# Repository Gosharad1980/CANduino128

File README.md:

# CANduino128
	- Break-out board pour la carte Olimex AVR-H128-CAN
	- Carte sur base d'AVR AT90CAN128
		- PC104 form factor
		- CAN network
		- SPI
		- I2C
		- bus d'addresse/Data externe via 74AHC373

# Board details

# Other
If you're happy by my work ... put a star ;-)

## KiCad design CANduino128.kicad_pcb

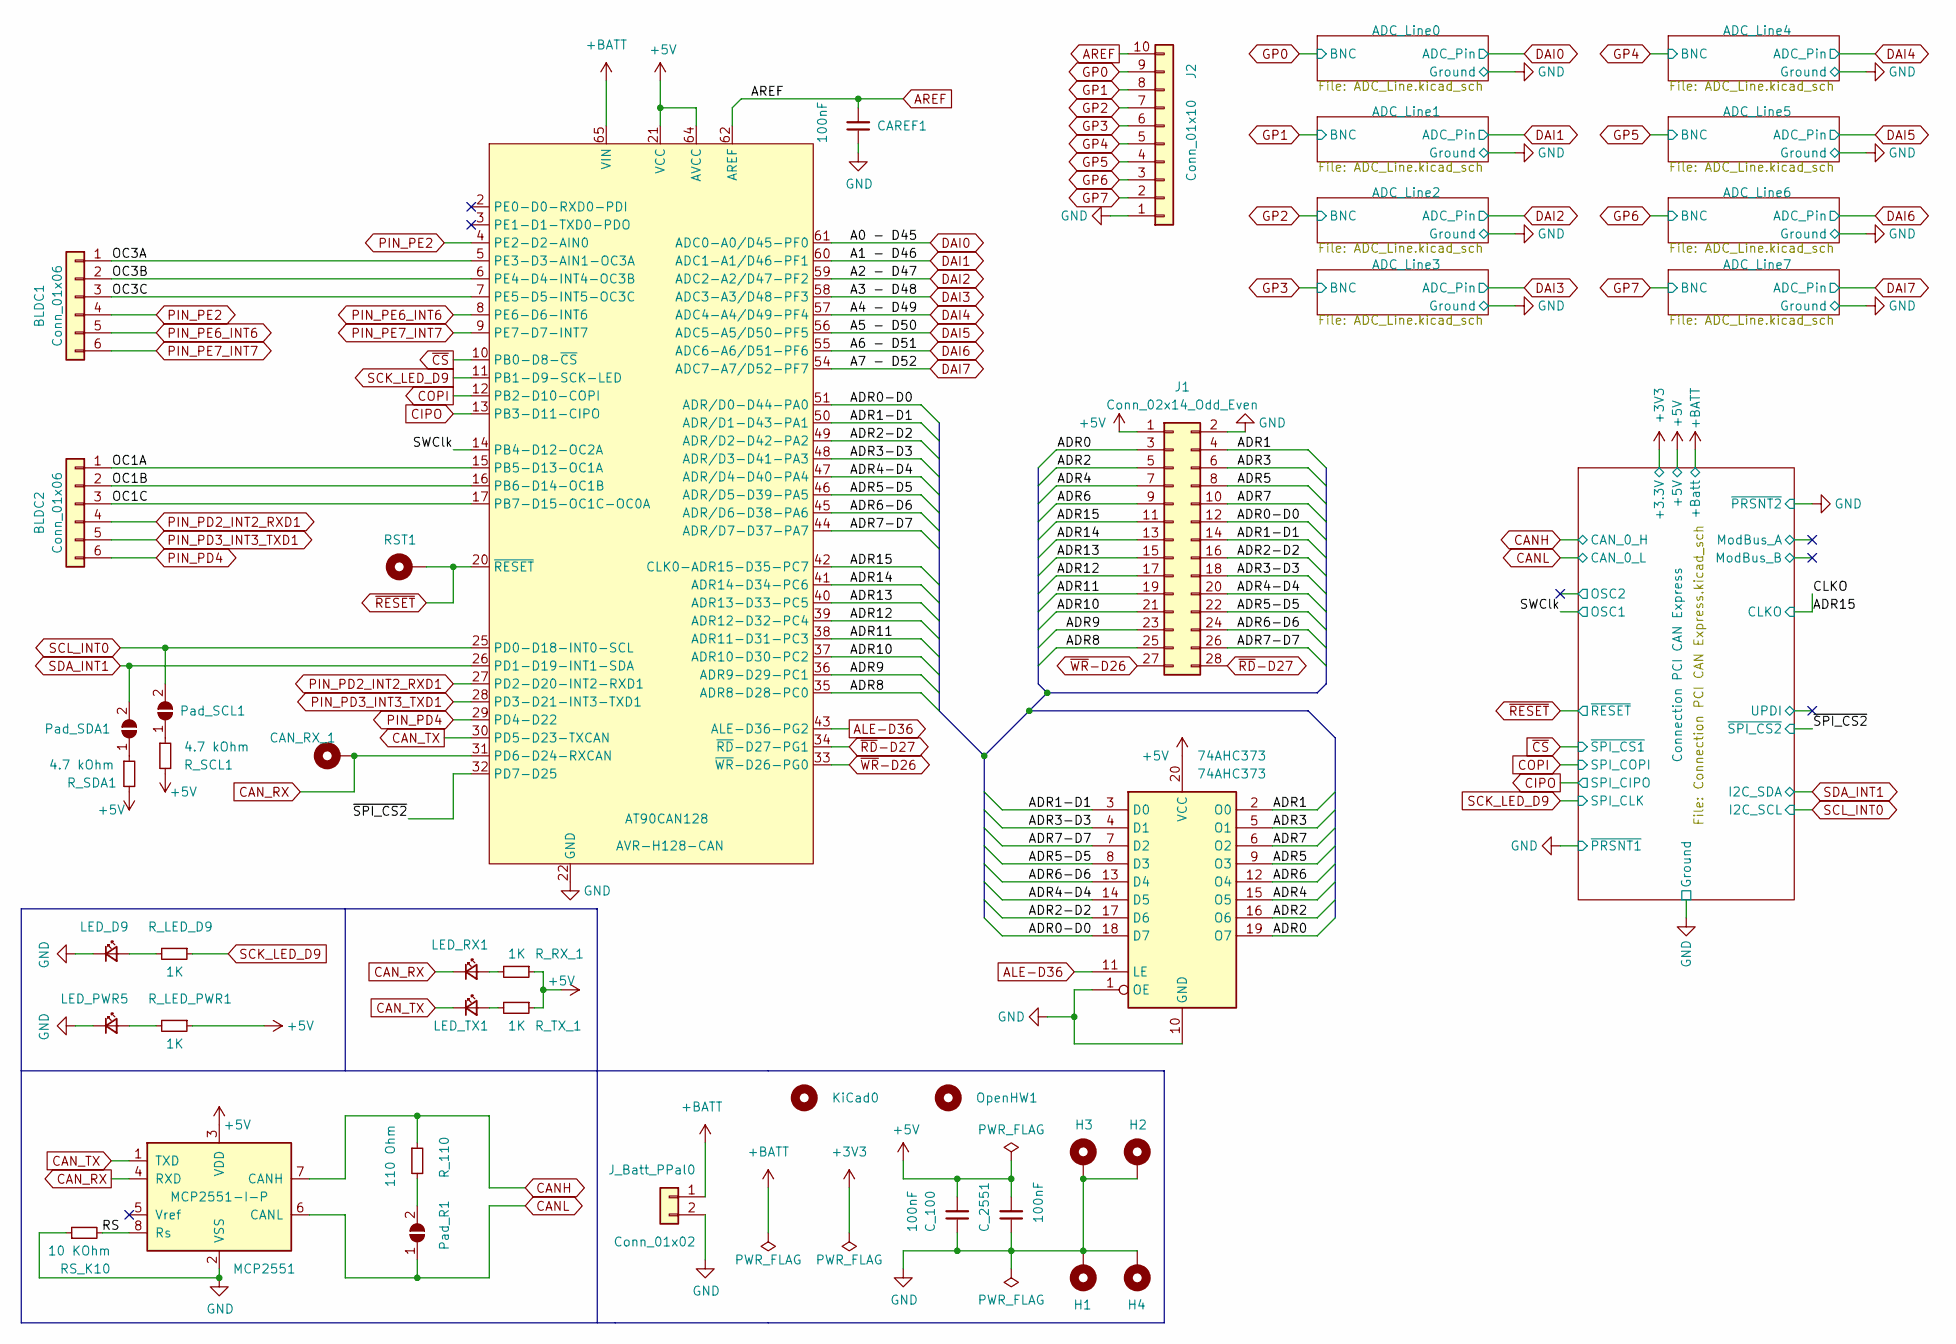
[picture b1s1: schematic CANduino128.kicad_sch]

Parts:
74AHC373: 74AHC373; SO-20_12.8x7.5mm_P1.27mm
AT90CAN128: AVR-H128-CAN; AVR_H128-CAN
BLDC1, BLDC2: Conn_01x06; TerminalBlock_Phoenix_MKDS-1,5-6-5.08_1x06_P5.08mm_Horizont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
CAN_RX_1: MountingHole_Pad; SolderWire-0.1sqmm_1x01_D0.4mm_OD1mm
CAREF1: 100nF; C_1210_3225Metric_Pad1.33x2.70mm_HandSolder
C_100, C_2551: 100nF; C_1210_3225Metric_Pad1.33x2.70mm_HandSolder
H1, H2, H3, H4: MountingHole_Pad; MountingHole_3.2mm_M3_Pad_Via
J1: Conn_02x14_Odd_Even; PinHeader_2x14_P2.54mm_Vertical
J2: Conn_01x10; TerminalBlock_Phoenix_MKDS-1,5-10-5.08_1x10_P5.08mm_Horizon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
J_Batt_PPal0: Conn_01x02; TerminalBlock_TE_282834-2_1x02_P2.54mm_Horizontal
KiCad0: MountingHole; KiCad-Logo2_5mm_SilkScreen
LED_D9: LED; LED_1210_3225Metric_Pad1.42x2.65mm_HandSolder
LED_PWR5: LED; LED_1210_3225Metric_Pad1.42x2.65mm_HandSolder
LED_RX1: LED; LED_1210_3225Metric_Pad1.42x2.65mm_HandSolder
LED_TX1: LED; LED_1210_3225Metric_Pad1.42x2.65mm_HandSolder
MCP2551: MCP2551-I-P; DIP-8_W7.62mm_Socket
OpenHW1: MountingHole; OSHW-Logo2_7.3x6mm_SilkScreen
Pad_R1: SolderJumper_2_Open; PinHeader_1x02_P2.54mm_Vertical
Pad_SCL1: SolderJumper_2_Open; SolderJumper-2_P1.3mm_Open_TrianglePad1.0x1.5mm
Pad_SDA1: SolderJumper_2_Open; SolderJumper-2_P1.3mm_Open_TrianglePad1.0x1.5mm
RST1: MountingHole_Pad; TestPoint_Pad_D1.0mm
RS_K10: 10 KOhm; R_1210_3225Metric_Pad1.30x2.65mm_HandSolder
R_110: 110 Ohm; R_1210_3225Metric_Pad1.30x2.65mm_HandSolder
R_LED_D9: 1K; R_1210_3225Metric_Pad1.30x2.65mm_HandSolder
R_LED_PWR1: 1K; R_1210_3225Metric_Pad1.30x2.65mm_HandSolder
R_RX_1: 1K; R_1210_3225Metric_Pad1.30x2.65mm_HandSolder
R_SCL1: 4.7 kOhm; R_1210_3225Metric_Pad1.30x2.65mm_HandSolder
R_SDA1: 4.7 kOhm; R_1210_3225Metric_Pad1.30x2.65mm_HandSolder
R_TX_1: 1K; R_1210_3225Metric_Pad1.30x2.65mm_HandSolder

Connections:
+5V: 74AHC373.20 (VCC), AT90CAN128.21 (VCC), AT90CAN128.52 (VCC), AT90CAN128.64 (AVCC), C_100.2, C_2551.2, J1.1, MCP2551.3 (VDD), R_LED_PWR1.1, R_RX_1.1, R_SCL1.2, R_SDA1.2, R_TX_1.1; also elsewhere on the board
+BATT: AT90CAN128.65 (VIN), J_Batt_PPal0.1; also elsewhere on the board
/ADR0: 74AHC373.19 (O7), J1.3
/ADR0-D0: 74AHC373.18 (D7), AT90CAN128.51 (ADR/D0-D44-PA0), J1.12
/ADR1: 74AHC373.2 (O0), J1.4
/ADR1-D1: 74AHC373.3 (D0), AT90CAN128.50 (ADR/D1-D43-PA1), J1.14
/ADR2: 74AHC373.16 (O6), J1.5
/ADR2-D2: 74AHC373.17 (D6), AT90CAN128.49 (ADR/D2-D42-PA2), J1.16
/ADR3: 74AHC373.5 (O1), J1.6
/ADR3-D3: 74AHC373.4 (D1), AT90CAN128.48 (ADR/D3-D41-PA3), J1.18
/ADR4: 74AHC373.15 (O5), J1.7
/ADR4-D4: 74AHC373.14 (D5), AT90CAN128.47 (ADR/D4-D40-PA4), J1.20
/ADR5: 74AHC373.9 (O3), J1.8
/ADR5-D5: 74AHC373.8 (D3), AT90CAN128.46 (ADR/D5-D39-PA5), J1.22
/ADR6: 74AHC373.12 (O4), J1.9
/ADR6-D6: 74AHC373.13 (D4), AT90CAN128.45 (ADR/D6-D38-PA6), J1.24
/ADR7: 74AHC373.6 (O2), J1.10
/ADR7-D7: 74AHC373.7 (D2), AT90CAN128.44 (ADR/D7-D37-PA7), J1.26
/ADR8: AT90CAN128.35 (ADR8-D28-PC0), J1.25
/ADR9: AT90CAN128.36 (ADR9-D29-PC1), J1.23
/ADR10: AT90CAN128.37 (ADR10-D30-PC2), J1.21
/ADR11: AT90CAN128.38 (ADR11-D31-PC3), J1.19
/ADR12: AT90CAN128.39 (ADR12-D32-PC4), J1.17
/ADR13: AT90CAN128.40 (ADR13-D33-PC5), J1.15
/ADR14: AT90CAN128.41 (ADR14-D34-PC6), J1.13
/ADR15: AT90CAN128.42 (CLK0-ADR15-D35-PC7), J1.11; also elsewhere on the board
/OC1A: AT90CAN128.15 (PB5-D13-OC1A), BLDC2.1
/OC1B: AT90CAN128.16 (PB6-D14-OC1B), BLDC2.2
/OC1C: AT90CAN128.17 (PB7-D15-OC1C-OC0A), BLDC2.3
/OC3A: AT90CAN128.5 (PE3-D3-AIN1-OC3A), BLDC1.1
/OC3B: AT90CAN128.6 (PE4-D4-INT4-OC3B), BLDC1.2
/OC3C: AT90CAN128.7 (PE5-D5-INT5-OC3C), BLDC1.3
/RS: MCP2551.8 (Rs), RS_K10.2
/SWClk: AT90CAN128.14 (PB4-D12-OC2A); also elsewhere on the board
/~SPI_CS2: AT90CAN128.32 (PD7-D25); also elsewhere on the board
ALE-D36: 74AHC373.11 (LE), AT90CAN128.43 (ALE-D36-PG2)
AREF: AT90CAN128.62 (AREF), CAREF1.2, J2.10
CANH: MCP2551.7 (CANH), R_110.1; also elsewhere on the board
CANL: MCP2551.6 (CANL), Pad_R1.1 (A); also elsewhere on the board
CAN_RX: AT90CAN128.31 (PD6-D24-RXCAN), CAN_RX_1.1 (1_1), LED_RX1.1 (K), MCP2551.4 (RXD)
CAN_TX: AT90CAN128.30 (PD5-D23-TXCAN), LED_TX1.1 (K), MCP2551.1 (TXD)
CIPO: AT90CAN128.13 (PB3-D11-CIPO); also elsewhere on the board
COPI: AT90CAN128.12 (PB2-D10-COPI); also elsewhere on the board
DAI0: AT90CAN128.61 (ADC0-A0/D45-PF0); also elsewhere on the board
DAI1: AT90CAN128.60 (ADC1-A1/D46-PF1); also elsewhere on the board
DAI2: AT90CAN128.59 (ADC2-A2/D47-PF2); also elsewhere on the board
DAI3: AT90CAN128.58 (ADC3-A3/D48-PF3); also elsewhere on the board
DAI4: AT90CAN128.57 (ADC4-A4/D49-PF4); also elsewhere on the board
DAI5: AT90CAN128.56 (ADC5-A5/D50-PF5); also elsewhere on the board
DAI6: AT90CAN128.55 (ADC6-A6/D51-PF6); also elsewhere on the board
DAI7: AT90CAN128.54 (ADC7-A7/D52-PF7); also elsewhere on the board
GND: 74AHC373.1 (OE), 74AHC373.10 (GND), AT90CAN128.22 (GND), AT90CAN128.53 (GND), AT90CAN128.63 (GND), AT90CAN128.66 (PWRGND), CAREF1.1, C_100.1, C_2551.1, H1.1 (1_1), H2.1 (1_1), H3.1 (1_1), H4.1 (1_1), J1.2, J2.1, J_Batt_PPal0.2, LED_D9.1 (K), LED_PWR5.1 (K), MCP2551.2 (VSS), RS_K10.1; also elsewhere on the board
GP0: J2.9; also elsewhere on the board
GP1: J2.8; also elsewhere on the board
GP2: J2.7; also elsewhere on the board
GP3: J2.6; also elsewhere on the board
GP4: J2.5; also elsewhere on the board
GP5: J2.4; also elsewhere on the board
GP6: J2.3; also elsewhere on the board
GP7: J2.2; also elsewhere on the board
unnamed: LED_D9.2 (A), R_LED_D9.2
unnamed: LED_PWR5.2 (A), R_LED_PWR1.2
unnamed: LED_RX1.2 (A), R_RX_1.2
unnamed: LED_TX1.2 (A), R_TX_1.2
unnamed: Pad_R1.2 (B), R_110.2
unnamed: Pad_SCL1.1 (A), R_SCL1.1
unnamed: Pad_SDA1.1 (A), R_SDA1.1
PIN_PD2_INT2_RXD1: AT90CAN128.27 (PD2-D20-INT2-RXD1), BLDC2.4
PIN_PD3_INT3_TXD1: AT90CAN128.28 (PD3-D21-INT3-TXD1), BLDC2.5
PIN_PD4: AT90CAN128.29 (PD4-D22), BLDC2.6
PIN_PE2: AT90CAN128.4 (PE2-D2-AIN0), BLDC1.4
PIN_PE6_INT6: AT90CAN128.8 (PE6-D6-INT6), BLDC1.5
PIN_PE7_INT7: AT90CAN128.9 (PE7-D7-INT7), BLDC1.6
SCK_LED_D9: AT90CAN128.11 (PB1-D9-SCK-LED), R_LED_D9.1; also elsewhere on the board
SCL_INT0: AT90CAN128.25 (PD0-D18-INT0-SCL), Pad_SCL1.2 (B); also elsewhere on the board
SDA_INT1: AT90CAN128.26 (PD1-D19-INT1-SDA), Pad_SDA1.2 (B); also elsewhere on the board
~CS: AT90CAN128.10 (PB0-D8-~CS); also elsewhere on the board
~RD-D27: AT90CAN128.34 (~RD-D27-PG1), J1.28
~RESET: AT90CAN128.20 (~RESET), RST1.1 (1_1); also elsewhere on the board
~WR-D26: AT90CAN128.33 (~WR-D26-PG0), J1.27

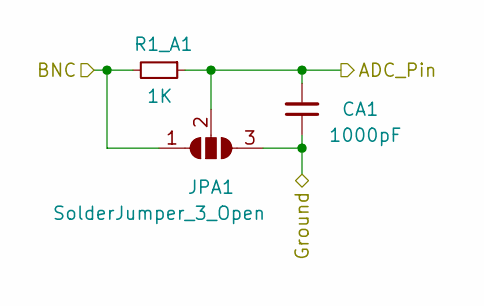
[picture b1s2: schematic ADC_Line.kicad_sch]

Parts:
CA1: 1000pF; C_1210_3225Metric_Pad1.33x2.70mm_HandSolder
JPA1: SolderJumper_3_Open; SolderJumper-3_P1.3mm_Open_RoundedPad1.0x1.5mm
R1_A1: 1K; R_1210_3225Metric_Pad1.30x2.65mm_HandSolder

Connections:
DAI0: CA1.2, JPA1.2 (C), R1_A1.1; also elsewhere on the board
GND: CA1.1, JPA1.3 (B); also elsewhere on the board
GP0: JPA1.1 (A), R1_A1.2; also elsewhere on the board

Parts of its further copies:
CA2, CA3, CA4, CA5, CA6, CA7, CA8: 1000pF; C_1210_3225Metric_Pad1.33x2.70mm_HandSolder
JPA2, JPA3, JPA4, JPA5, JPA6, JPA7, JPA8: SolderJumper_3_Open; SolderJumper-3_P1.3mm_Open_RoundedPad1.0x1.5mm
R1_A2, R1_A3, R1_A4, R1_A5, R1_A6, R1_A7, R1_A8: 1K; R_1210_3225Metric_Pad1.30x2.65mm_HandSolder

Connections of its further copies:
DAI1: CA2.2, JPA2.2 (C), R1_A2.1; also elsewhere on the board
DAI2: CA3.2, JPA3.2 (C), R1_A3.1; also elsewhere on the board
DAI3: CA4.2, JPA4.2 (C), R1_A4.1; also elsewhere on the board
DAI4: CA5.2, JPA5.2 (C), R1_A5.1; also elsewhere on the board
DAI5: CA6.2, JPA6.2 (C), R1_A6.1; also elsewhere on the board
DAI6: CA7.2, JPA7.2 (C), R1_A7.1; also elsewhere on the board
DAI7: CA8.2, JPA8.2 (C), R1_A8.1; also elsewhere on the board
GND: CA2.1, CA3.1, CA4.1, CA5.1, CA6.1, CA7.1, CA8.1, JPA2.3 (B), JPA3.3 (B), JPA4.3 (B), JPA5.3 (B), JPA6.3 (B), JPA7.3 (B), JPA8.3 (B); also elsewhere on the board
GP1: JPA2.1 (A), R1_A2.2; also elsewhere on the board
GP2: JPA3.1 (A), R1_A3.2; also elsewhere on the board
GP3: JPA4.1 (A), R1_A4.2; also elsewhere on the board
GP4: JPA5.1 (A), R1_A5.2; also elsewhere on the board
GP5: JPA6.1 (A), R1_A6.2; also elsewhere on the board
GP6: JPA7.1 (A), R1_A7.2; also elsewhere on the board
GP7: JPA8.1 (A), R1_A8.2; also elsewhere on the board

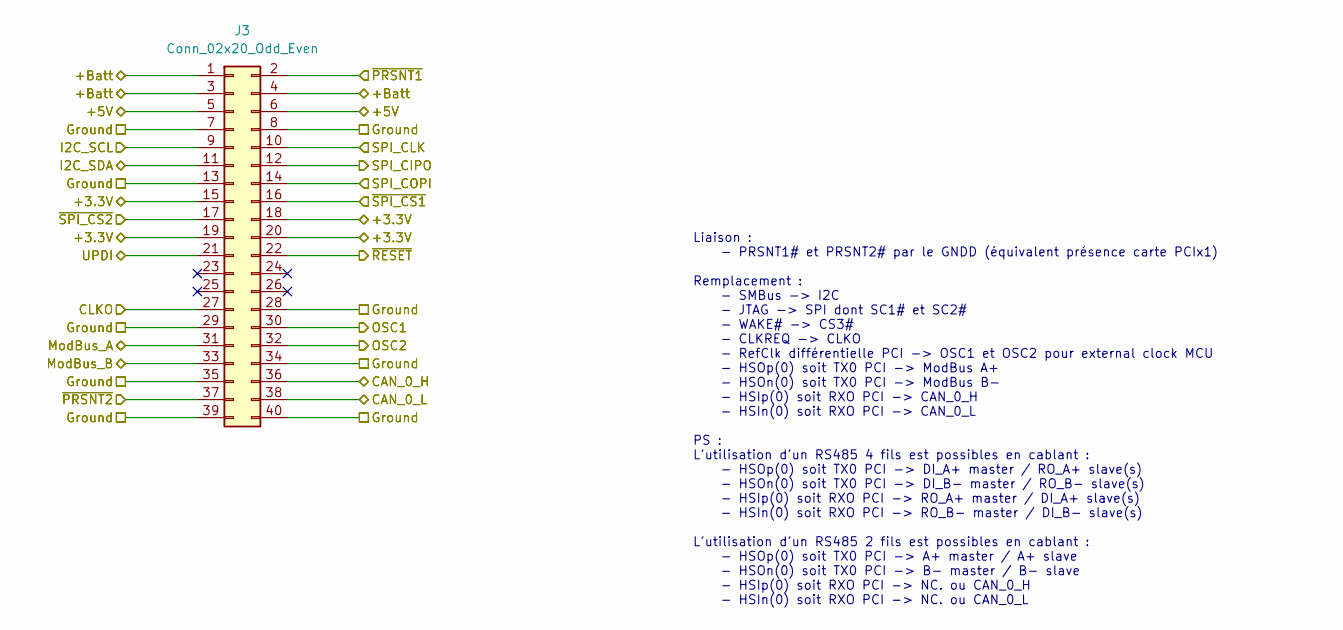
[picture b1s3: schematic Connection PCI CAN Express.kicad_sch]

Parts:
J3: Conn_02x20_Odd_Even; IDC-Header_2x20_P2.54mm_Vertical

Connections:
+3V3: J3.15, J3.18, J3.19, J3.20
+5V: J3.5, J3.6; also elsewhere on the board
+BATT: J3.1, J3.3, J3.4; also elsewhere on the board
/ADR15: J3.27; also elsewhere on the board
/Connection PCI CAN Express/ModBus_A: J3.31
/Connection PCI CAN Express/ModBus_B: J3.33
/Connection PCI CAN Express/OSC2: J3.32
/Connection PCI CAN Express/UPDI: J3.21
/SWClk: J3.30; also elsewhere on the board
/~SPI_CS2: J3.17; also elsewhere on the board
CANH: J3.36; also elsewhere on the board
CANL: J3.38; also elsewhere on the board
CIPO: J3.12; also elsewhere on the board
COPI: J3.14; also elsewhere on the board
GND: J3.2, J3.7, J3.8, J3.13, J3.28, J3.29, J3.34, J3.35, J3.37, J3.39, J3.40; also elsewhere on the board
SCK_LED_D9: J3.10; also elsewhere on the board
SCL_INT0: J3.9; also elsewhere on the board
SDA_INT1: J3.11; also elsewhere on the board
~CS: J3.16; also elsewhere on the board
~RESET: J3.22; also elsewhere on the board

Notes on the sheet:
Liaison : - PRSNT1# et PRSNT2# par le GNDD (équivalent présence carte PCIx1) Remplacement : - SMBus -> I2C - JTAG -> SPI dont SC1# et SC2# - WAKE# -> CS3# - CLKREQ -> CLKO - RefClk différentielle PCI -> OSC1 et OSC2 pour external clock MCU - HSOp(0) soit TX0 PCI -> ModBus A+ - HSOn(0) soit TX0 PCI 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

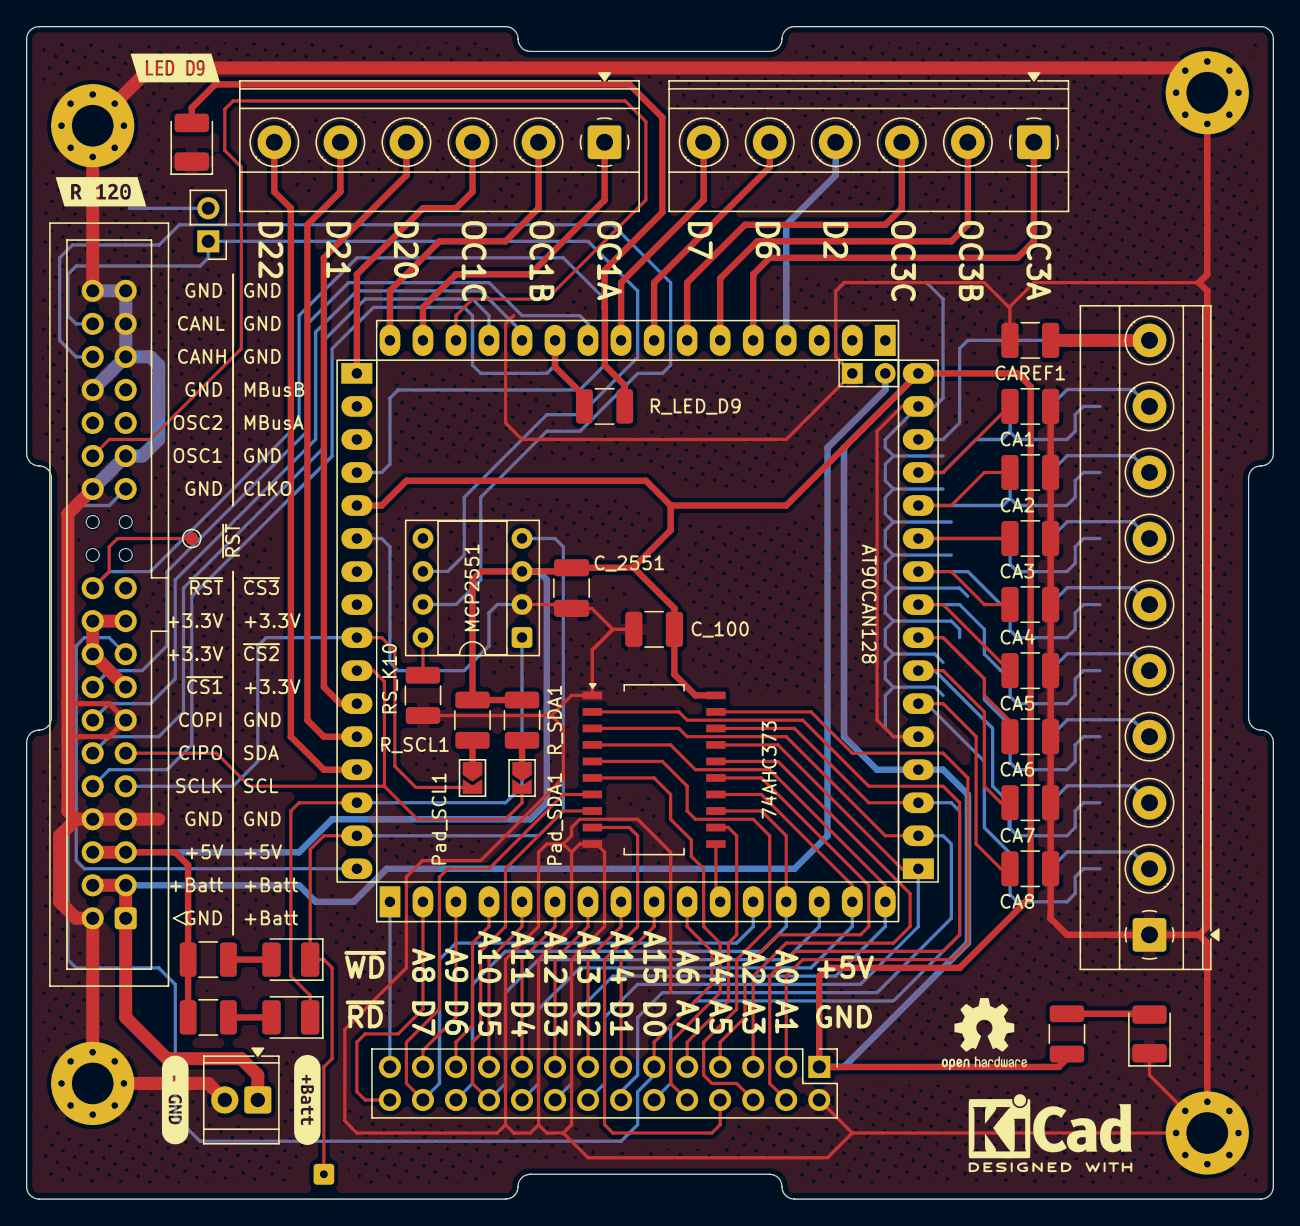
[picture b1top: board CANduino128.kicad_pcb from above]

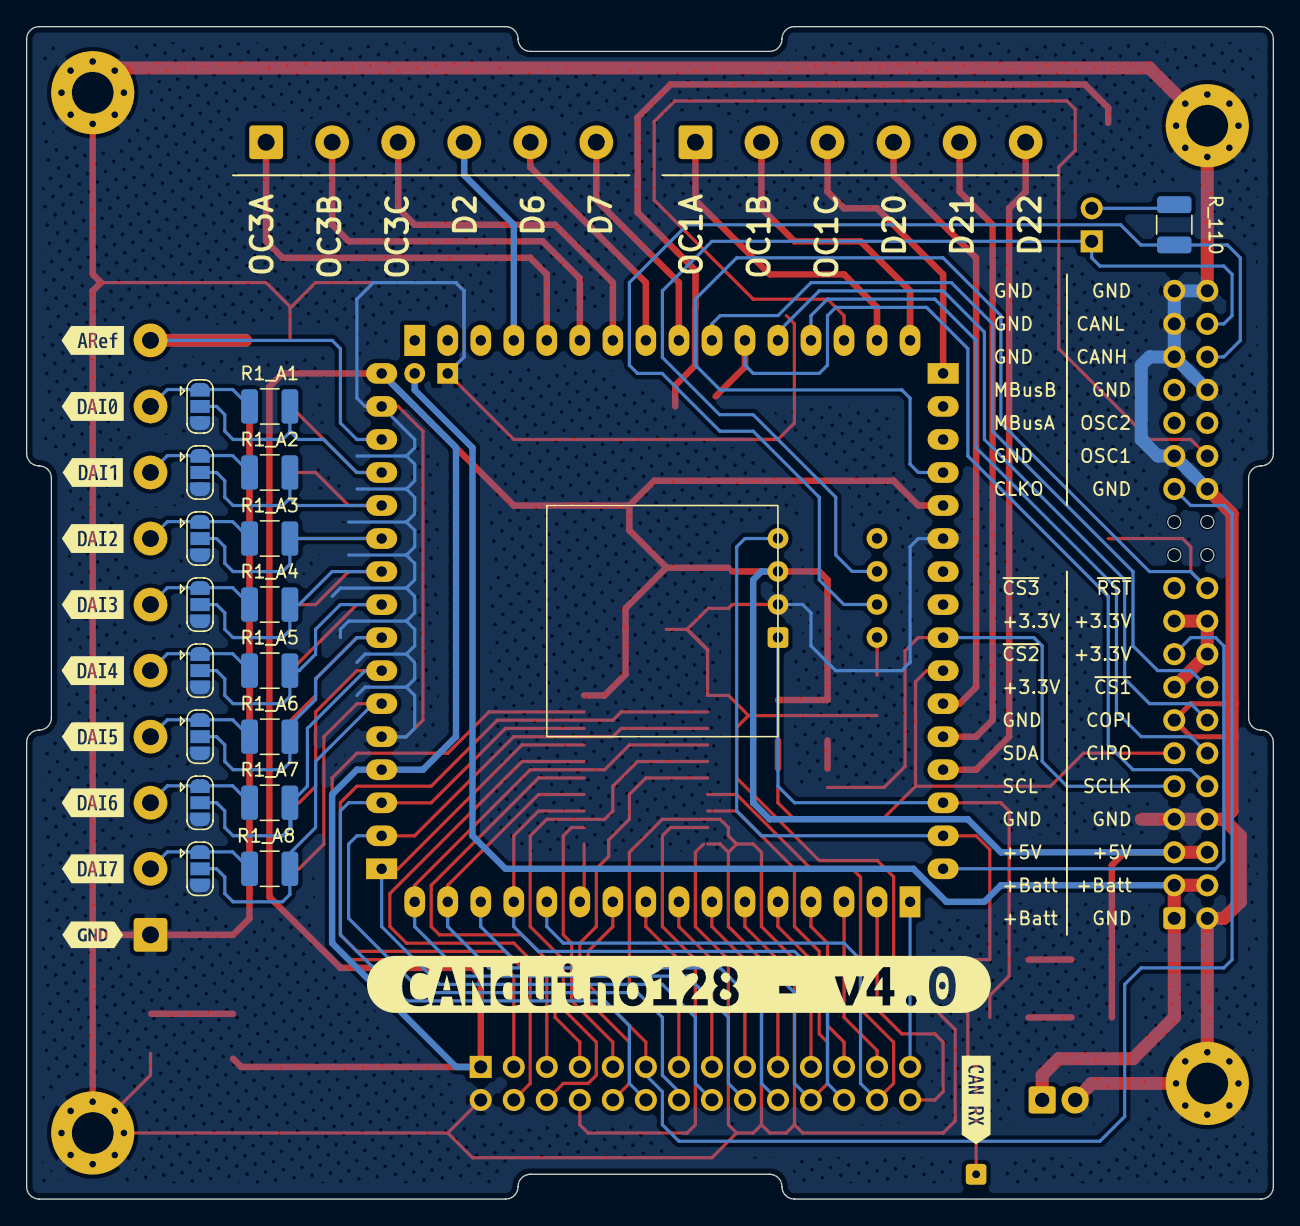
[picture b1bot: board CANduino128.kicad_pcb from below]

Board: 2 copper layers, 95.9 x 90.2 mm, 75 parts (29 on the bottom side), 81 nets.

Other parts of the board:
kibuzzard-62F694D7: G***; kibuzzard-62F694D7
kibuzzard-62F83662: G***; kibuzzard-62F83662
kibuzzard-638A835C: G***; kibuzzard-638A835C
kibuzzard-6252E5C3: G***; kibuzzard-6252E5C3
kibuzzard-62533B1F: G***; kibuzzard-62533B1F
kibuzzard-62799BC1: G***; kibuzzard-62799BC1
kibuzzard-638672AD: G***; kibuzzard-638672AD
kibuzzard-6315171A: G***; kibuzzard-6315171A
kibuzzard-6315172E: G***; kibuzzard-6315172E
kibuzzard-6315173E: G***; kibuzzard-6315173E
kibuzzard-63151701: G***; kibuzzard-63151701
kibuzzard-63151724: G***; kibuzzard-63151724
kibuzzard-63151737: G***; kibuzzard-63151737
kibuzzard-63151748: G***; kibuzzard-63151748
kibuzzard-63151750: G***; kibuzzard-63151750
kibuzzard-63867289: G***; kibuzzard-63867289

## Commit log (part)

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2022-06-12 Imported folder structure
2022-06-12 rev0.0
2022-08-07 Allez, on se fait une PC104 (ou autre, on verra) avec un bus custom (parce que le bus ISA c'est pas glop en terme de routage) !
2022-08-12 Ha ha ! Probablement un lancement en production. En tout cas à 99%. - quelques replacement de Pad - correction de Silkscreen
2022-08-14 A envoyer en prod. - câblage Reset (avec "via") - câblage T0_0C0x - câblage ICP1 - correction silskreen
2022-08-23 Dernier run DRC pour production :)
2022-08-23 Figeage v3.0 PC104 ISA bus pour production :)
2022-09-04 Petite study du form factor PC104 version LibreCube pour CubeSAT
2022-11-22 Passage full en form-factor PCI_CAN_Express perso.
2022-11-22 Allez on entame les travaux ... et y'a du taf.
2022-11-27 Houlà ! On y est presque ! Un peu de silkscreen à mettre à jour et on aura une révision livrable.
2022-11-27 Bin ouais, y'a changement d'interfaçage avec le monde extérieure ... puisqu'on change de form-factor.
2022-11-27 - Carry-over de la correction sur inversion des bornes d'entrées/sorties des circuits des pins analogiques. - Correction de plusieurs valeurs électriques sur le port ISA8 des pins non utilisées - Res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
    - Préparation marquage v3.1
    - Génération des fichiers de fabrication par principe
2022-11-28 On carréïse le form-factor avec des angles à 1.2mm de rayon On branche le +Batt sur la port ISA en lieu et place du +12V On arrange le silkscreen du port ISA pour tenir compte des +5V et des GND de b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
2022-11-29 Silkscreen terminé. Bon pour release après une dernière vérif.
2022-11-29 It's the fanal countdown tadadaaaada tadada ! Bon pour v3.1
2022-12-02 Avec les réglages "Rancunes"
2022-12-03 Adieu le connecteur sous l'AT90CAN128
2022-12-03 Bon on split officiellement le projet en deux branches fonction du form-factor
2022-12-04 Le commit où on arrondi les angles ... et où on met à jour le DRC de JLCPCB.
2022-12-05 Bon on retire les arrondi pour voir si c'est ça qui bloque JLCPCB
2023-03-27 KiCad 7.0 SPI_CS3 Reste simplification du chemin Redondance alim +5V
    Mais surtout KiCad 7.0 qui empêche la rétrocompatibilité avec les version antérieure sous KiCad 6.x
2023-04-01 Bye bye KiCad 6 Vive KiCad 7 !!
2023-04-01 Petites correction de GND qui étaient des "Oval" et non pas des "Circular"
2023-04-02 Régénération du plan de masse Création des Gerber
2023-04-03 Elargissement des pistes d'alim de 0.25mm à 0.5mm Application de règles d'un prof random sur internet Régénération des fichiers gerber
2023-04-17 Mise à jour du DRC ... argh.
2023-04-29 Mini update du routage de +Batt et +5V
2023-05-23 "Correction" du bug sur les nombres à plus de chiffres significatifs sur les plans de masse Ajout des teardrops
2023-05-23 Ajout du marquage JLCJLCJLCJLC
2023-06-14 Régen de la BOM pour le soudage des composants.
2023-08-18 Correction clearance de bord de carte à 0.635mm
2023-09-07 Mise à niveau du pin-out avec l'autre form-factor
2023-09-16 Houlà y'a eu du taf ! - fin MAJ pin-out iso v4.0a - ajout demux CD4555 pour lignes DRQ1/2/3 sur le connecteur ISA8 - pifiou ! les modifs de routages
2023-09-17 YES ! On a réussi à les câbler en /CS2 et /CS3 comme des chip select de la V4.0a
2023-09-17 Déplacement des connecteurs BLDC Reroute Ajout d'un connecteur ICSP de type USBAsp
2023-10-01 On se cherche encore sur les /CS qui vont sur les DRQx ou les /DRAQx
2024-02-26 Last version pour la v3.2 On arrête les frais sur cette carte
2024-06-10 KiCad 8
2025-02-19 Passage à KiCad 9.0 RC1
2025-02-19 Ajout des docs Pdf
2025-04-27 Readme update + photos
2025-04-27 Pdf et doc update
2025-04-27 Readme update
2025-05-01 3D models update
2025-05-01 Package3D model list update
2025-07-13 Adding : licence file for CC-BY-SA-4.0
